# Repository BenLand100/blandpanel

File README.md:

# BLandPanel

This aims to be a reference design for a DYI telescope automated flat panel.
Any RP2040 dev board, or similar device, capable of running MicroPython,
a PWM modulated servo, and some commodity electronics components make up the
electronics. Some Python and C++ for writing the firmware and software driver
(respectively - which is quite ironic) to allow INDI capable clients to control
the device and a bit of CAD and 3D printing to hold it all together.

The flat panel ~~and CAD itself are~~ is TBD.

## RP2040 Firmware

Firmware for the RP2040 microcontroller is available in `rpico-firmare`.

Any RP2040 dev board with some reasonable pinout will work. This repo is tested
and configured for the vanilla Raspberry Pi Pico using some arbitrary GPIO and 
one optional-ish ADC pin. A small current driver for the LED panel will be 
required. 

## INDI driver

A driver based heavily off the reference INDI driver that can control the 
firmware is available in `indi-driver`.

## ASCOM driver

The firmware also impelemnts (untested) the flat panel serial protocol found in 
[DarkSkyGeek's ascom-flat-panel repo](https://github.com/jlecomte/ascom-flat-panel/)
so the ASCOM driver found there would very likely control this firmware fine.

## CAD Design

There is a FreeCAD project in the `design` directory along with exported models
of the current build. This is very much a WIP and the current model is a test 
design primarily to figure out what needs to be changed for the next revision.

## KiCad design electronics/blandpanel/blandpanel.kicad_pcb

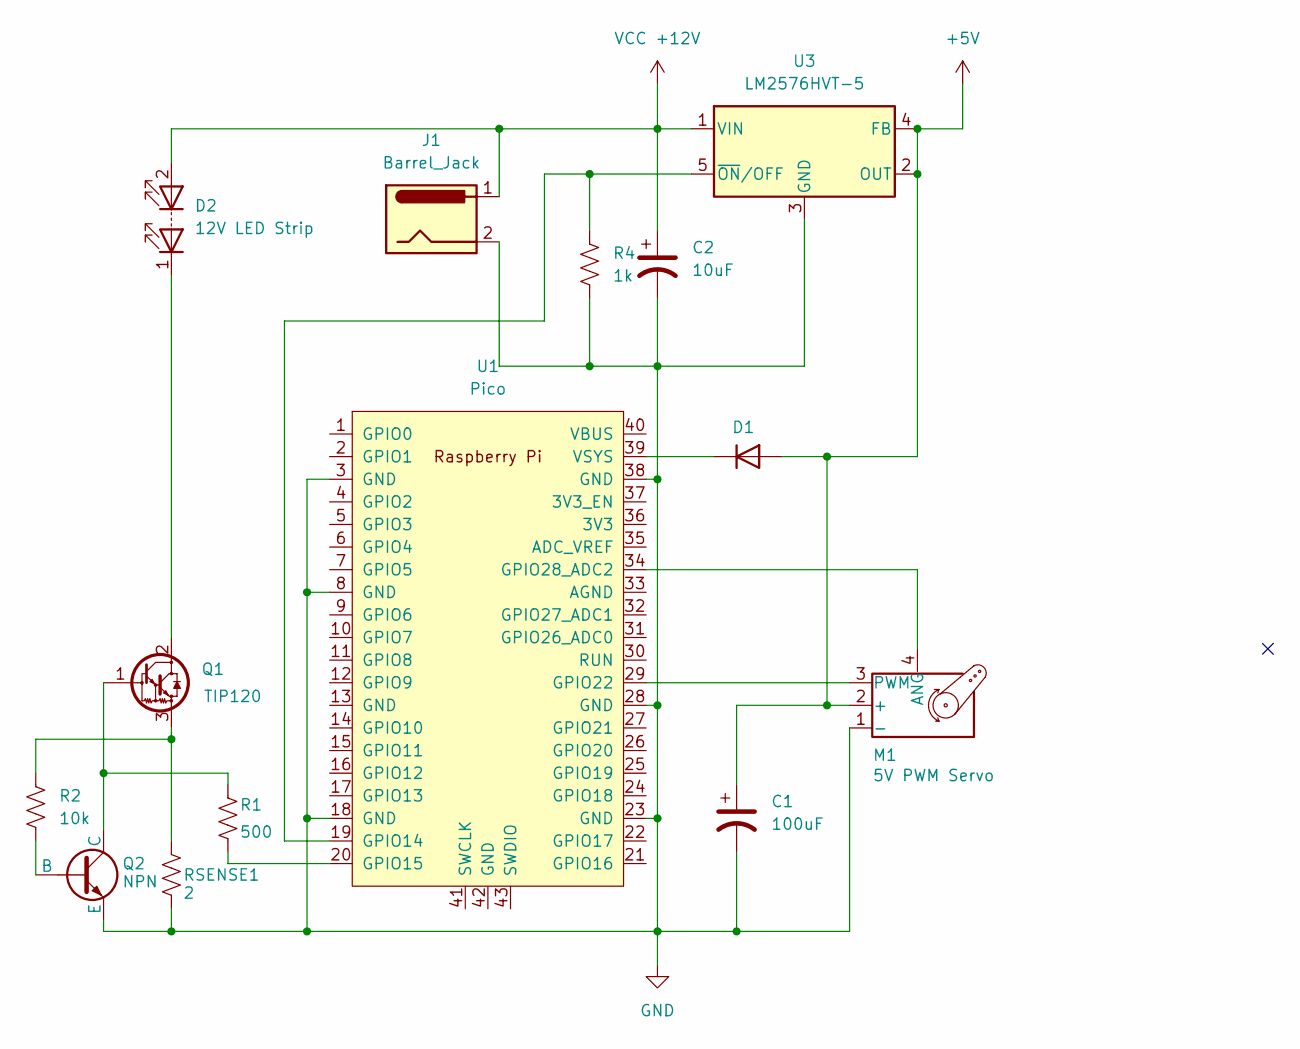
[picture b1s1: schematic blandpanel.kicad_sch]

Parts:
C1: 100uF; CP_Radial_D8.0mm_P2.50mm
C2: 10uF; CP_Radial_D8.0mm_P2.50mm
D1: 40V; D_DO-41_SOD81_P10.16mm_Horizontal
D2: 12V LED Strip; PinHeader_1x02_P2.54mm_Vertical
J1: Barrel_Jack; BarrelJack_Horizontal
M1: 5V PWM Servo; PinHeader_1x04_P2.54mm_Vertical
Q1: TIP120; TO-220-3_Vertical
Q2: NPN; TO-92
R1: 500; R_Axial_DIN0207_L6.3mm_D2.5mm_P10.16mm_Horizontal
R2: 10k; R_Axial_DIN0207_L6.3mm_D2.5mm_P10.16mm_Horizontal
R4: 1k
RSENSE1: 2; R_Axial_DIN0207_L6.3mm_D2.5mm_P10.16mm_Horizontal
U1: Pico; RPi_Pico_SMD_TH
U3: LM2576HVT-5; TO-220-5_Vertical

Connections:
+5V: C1.1, D1.2 (A), M1.2 (+), U3.2 (OUT), U3.4 (FB)
GND: C1.2, C2.2, J1.2, M1.1 (-), Q2.3 (E), R4.2, RSENSE1.2, U1.3 (GND), U1.8 (GND), U1.18 (GND), U1.23 (GND), U1.28 (GND), U1.38 (GND), U3.3 (GND)
unnamed: D1.1 (K), U1.39 (VSYS)
unnamed: D2.1 (K), Q1.2 (C)
unnamed: M1.4 (ANG), U1.34 (GPIO28_ADC2)
unnamed: M1.3 (PWM), U1.29 (GPIO22)
unnamed: Q1.1 (B), Q2.1 (C), R1.1
unnamed: Q1.3 (E), R2.1, RSENSE1.1
unnamed: Q2.2 (B), R2.2
unnamed: R4.1, U1.19 (GPIO14), U3.5 (~ON/OFF)
unnamed: R1.2, U1.20 (GPIO15)
VCC +12V: C2.1, D2.2 (A), J1.1, U3.1 (VIN)

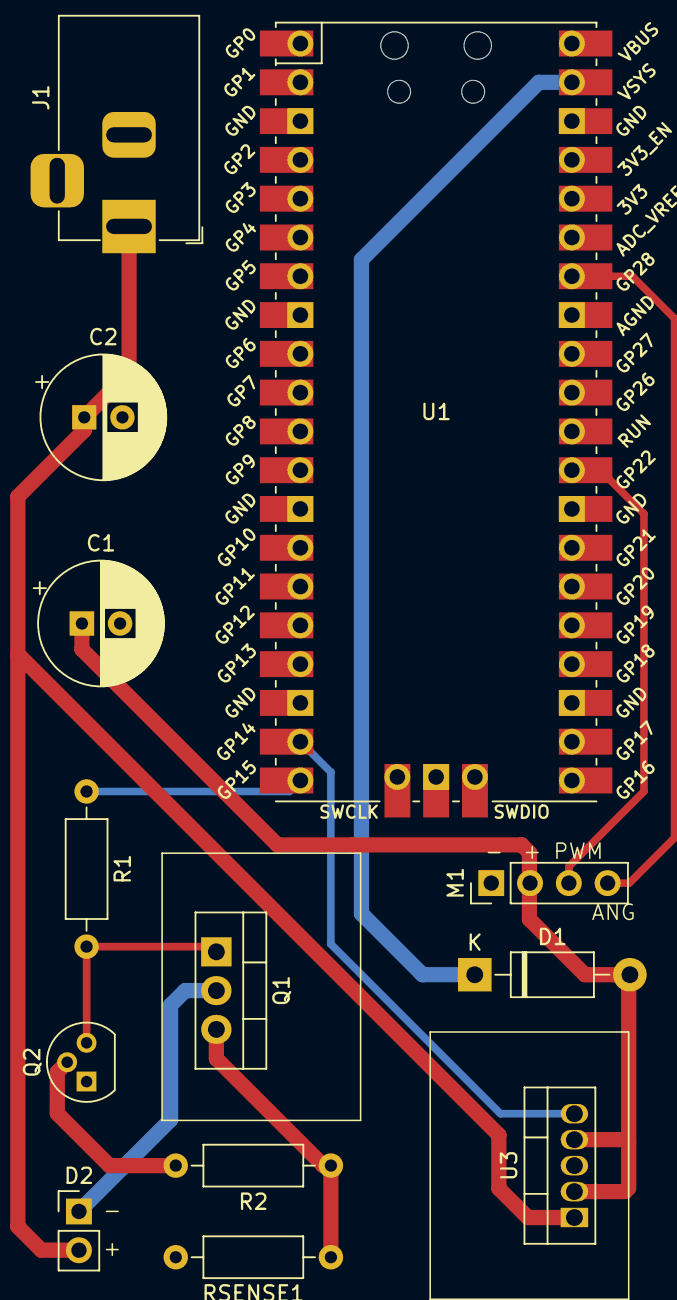
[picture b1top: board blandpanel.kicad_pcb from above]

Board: 2 copper layers, 13 parts (0 on the bottom side), 12 nets.

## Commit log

2025-01-12 MVP commit
2025-01-12 Add CAD design
2025-01-12 Fix missing cable channel for servo
2025-01-12 Add full design
2025-01-13 Add estop; fix clearance issues on design.
2025-01-18 Add electronics and final design
2025-01-30 Updates for semi-final design
